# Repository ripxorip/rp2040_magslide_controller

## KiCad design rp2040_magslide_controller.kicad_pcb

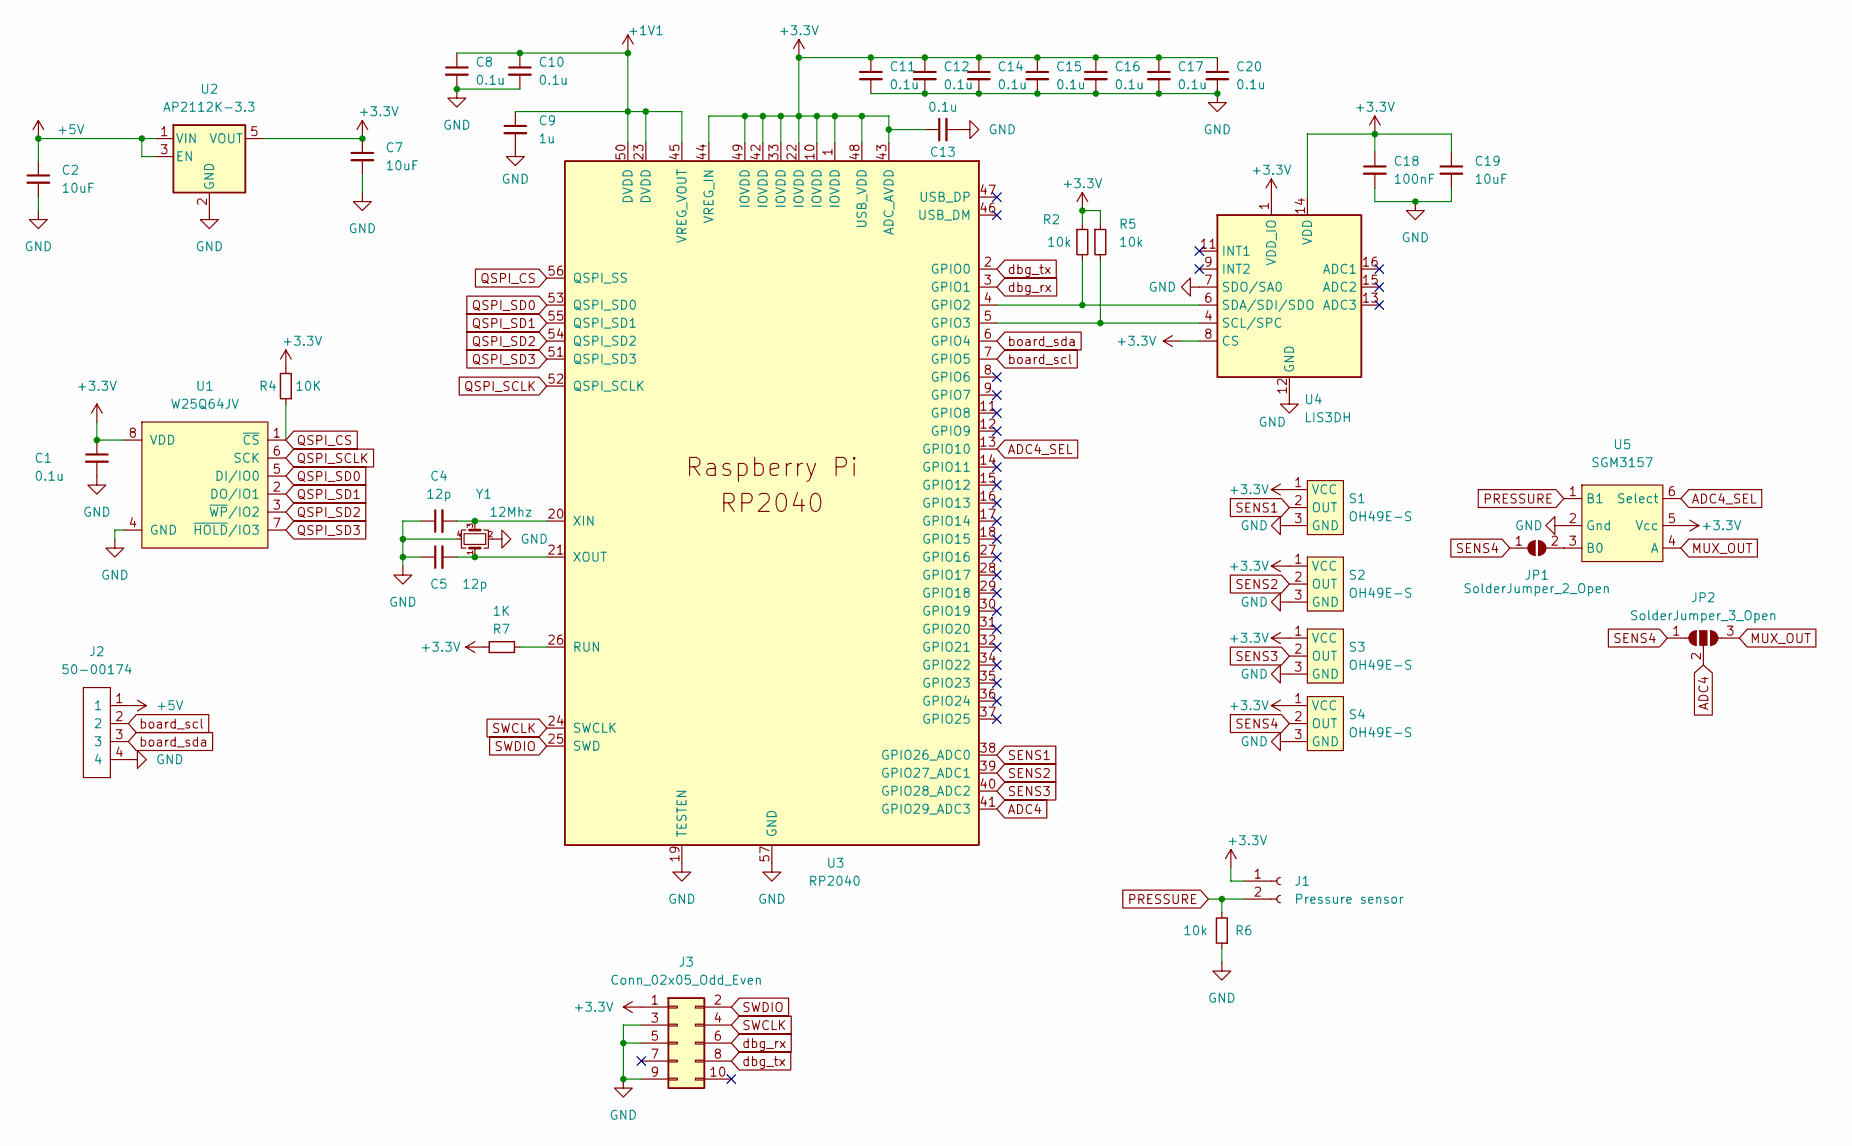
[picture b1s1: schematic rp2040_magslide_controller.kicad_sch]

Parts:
C1, C8, C10, C11, C12, C13, C14, C15, C16, C17, C20: 0.1u; C_0402_1005Metric
C2, C7, C19: 10uF; C_0603_1608Metric
C4, C5: 12p; C_0402_1005Metric
C9: 1u; C_0603_1608Metric
C18: 100nF; C_0402_1005Metric
J1: Pressure sensor; PinHeader_1x02_P1.00mm_Vertical
J2: 50-00174; 54-00174
J3: Conn_02x05_Odd_Even; Tag-Connect_TC2050-IDC-NL_2x05_P1.27mm_Vertical
JP1: SolderJumper_2_Open; SolderJumper-2_P1.3mm_Open_RoundedPad1.0x1.5mm
JP2: SolderJumper_3_Open; SolderJumper-3_P1.3mm_Open_RoundedPad1.0x1.5mm
R2, R5, R6: 10k; R_0402_1005Metric
R4: 10K; R_0402_1005Metric
R7: 1K; R_0402_1005Metric
S1, S2, S3, S4: OH49E-S; SOT-23
U1: W25Q64JV; SOP-8_5.28x5.23mm_P1.27mm
U2: AP2112K-3.3; SOT-23-5
U3: RP2040; RP2040-QFN-56
U4: LIS3DH; LGA-16_3x3mm_P0.5mm_LayoutBorder3x5y
U5: SGM3157; SC70-6
Y1: 12Mhz; Crystal_SMD_3225-4Pin_3.2x2.5mm

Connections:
+1V1: C8.1, C9.1, C10.1, U3.23 (DVDD), U3.45 (VREG_VOUT), U3.50 (DVDD)
+3V3: C1.1, C7.1, C11.1, C12.1, C13.1, C14.1, C15.1, C16.1, C17.1, C18.1, C19.1, C20.1, J1.1, J3.1, R2.1, R4.2, R5.1, R7.1, S1.1 (VCC), S2.1 (VCC), S3.1 (VCC), S4.1 (VCC), U1.8 (VDD), U2.5 (VOUT), U3.1 (IOVDD), U3.10 (IOVDD), U3.22 (IOVDD), U3.33 (IOVDD), U3.42 (IOVDD), U3.43 (ADC_AVDD), U3.44 (VREG_IN), U3.48 (USB_VDD), U3.49 (IOVDD), U4.1 (VDD_IO), U4.8 (CS), U4.14 (VDD), U5.5 (Vcc)
+5V: C2.1, J2.1, U2.1 (VIN), U2.3 (EN)
ADC4: JP2.2 (C), U3.41 (GPIO29_ADC3)
ADC4_SEL: U3.13 (GPIO10), U5.6 (Select)
GND: C1.2, C2.2, C4.1, C5.1, C7.2, C8.2, C9.2, C10.2, C11.2, C12.2, C13.2, C14.2, C15.2, C16.2, C17.2, C18.2, C19.2, C20.2, J2.4, J3.3, J3.5, J3.9, R6.1, S1.3 (GND), S2.3 (GND), S3.3 (GND), S4.3 (GND), U1.4 (GND), U2.2 (GND), U3.19 (TESTEN), U3.57 (GND), U4.5 (GND), U4.7 (SDO/SA0), U4.10 (GND), U4.12 (GND), U5.2 (Gnd), Y1.2, Y1.4
MUX_OUT: JP2.3 (B), U5.4 (A)
unnamed: C4.2, U3.20 (XIN), Y1.3
unnamed: C5.2, U3.21 (XOUT), Y1.1
unnamed: JP1.2 (B), U5.3 (B0)
unnamed: R2.2, U3.4 (GPIO2), U4.6 (SDA/SDI/SDO)
unnamed: R5.2, U3.5 (GPIO3), U4.4 (SCL/SPC)
unnamed: R7.2, U3.26 (RUN)
PRESSURE: J1.2, R6.2, U5.1 (B1)
QSPI_CS: R4.1, U1.1 (~CS), U3.56 (QSPI_SS)
QSPI_SCLK: U1.6 (SCK), U3.52 (QSPI_SCLK)
QSPI_SD0: U1.5 (DI/IO0), U3.53 (QSPI_SD0)
QSPI_SD1: U1.2 (DO/IO1), U3.55 (QSPI_SD1)
QSPI_SD2: U1.3 (~WP/IO2), U3.54 (QSPI_SD2)
QSPI_SD3: U1.7 (~HOLD/IO3), U3.51 (QSPI_SD3)
SENS1: S1.2 (OUT), U3.38 (GPIO26_ADC0)
SENS2: S2.2 (OUT), U3.39 (GPIO27_ADC1)
SENS3: S3.2 (OUT), U3.40 (GPIO28_ADC2)
SENS4: JP1.1 (A), JP2.1 (A), S4.2 (OUT)
SWCLK: J3.4, U3.24 (SWCLK)
SWDIO: J3.2, U3.25 (SWD)
board_scl: J2.2, U3.7 (GPIO5)
board_sda: J2.3, U3.6 (GPIO4)
dbg_rx: J3.6, U3.3 (GPIO1)
dbg_tx: J3.8, U3.2 (GPIO0)

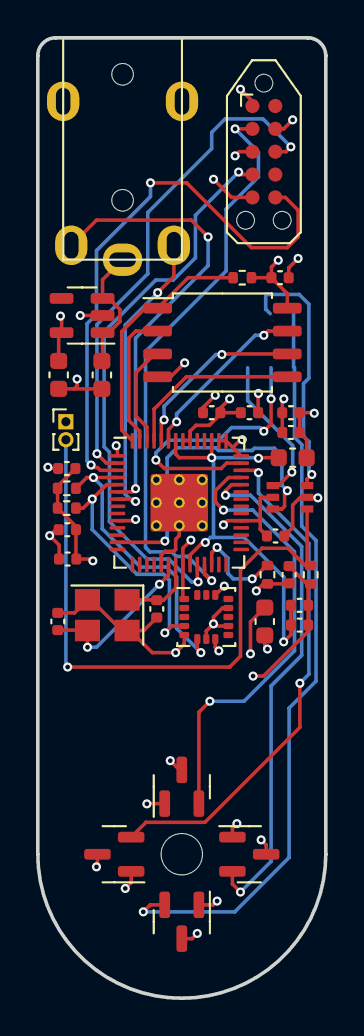
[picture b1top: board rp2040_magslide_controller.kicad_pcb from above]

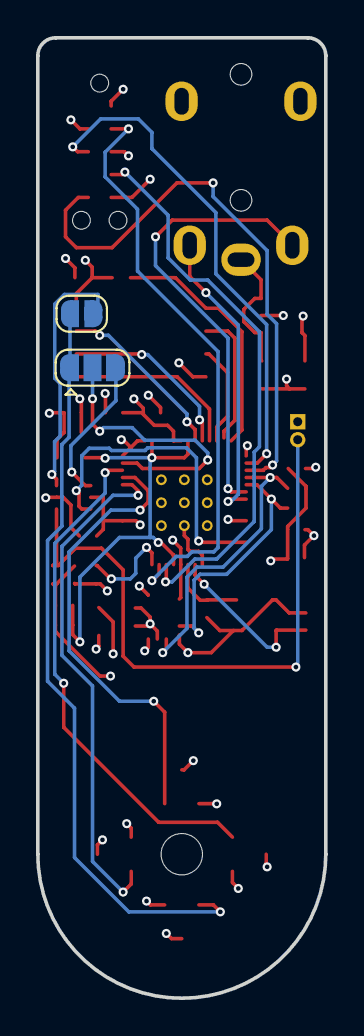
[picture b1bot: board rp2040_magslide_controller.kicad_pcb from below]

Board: 4 copper layers, 16.0 x 53.4 mm, 39 parts (2 on the bottom side), 30 nets.

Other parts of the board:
H1: MountingHole; MagHole

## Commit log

2022-04-11 Initial commit..
2022-04-11 DRC pass, next up _review_
2022-04-13 WIP for layout, need new footprint for rp2040 for some reason...
2022-04-14 Routing done, next up fix the JLCPCB-part numbers then order
2022-04-15 Adds SOP8 flash instead
2022-05-15 Adds DXFs for outlines
2022-05-16 Routing and DRC Done - Next up REVIEW
2022-05-16 Updated JLCPCB
2022-05-16 Adds fabrication files
2022-05-16 Needs new fabrication files for _some_ reason
2022-05-17 This is ordered from JLCPCB
